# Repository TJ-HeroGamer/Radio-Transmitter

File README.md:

# Radio-Transmitter
Used for theatres to troubleshoot systems. A tool used to remove the issue of a broken radio microphone whilst troubleshooting. This will solely test the radio signal is working properly/ there is no interferance. Everything is very much WIP at the moment. the circuit diagrams will get more complex

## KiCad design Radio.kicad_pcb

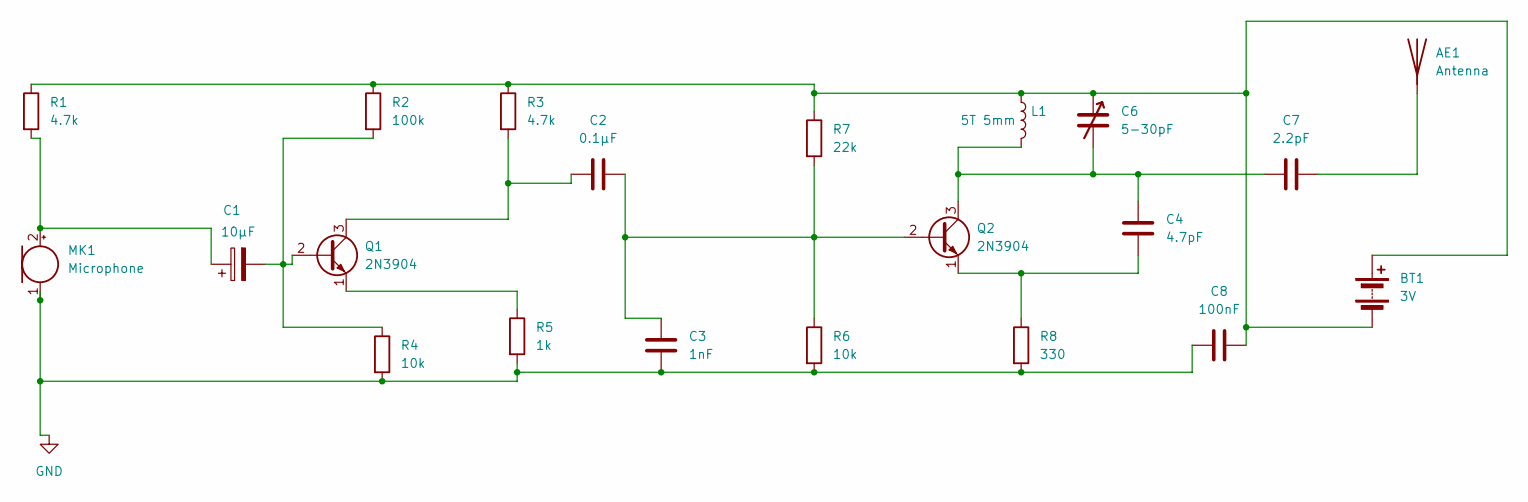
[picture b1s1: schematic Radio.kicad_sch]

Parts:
AE1: Antenna; TestPoint_Pad_D2.0mm
BT1: 3V; PinHeader_1x02_P2.54mm_Vertical
C1: 10μF; CP_Radial_D5.0mm_P2.50mm
C2: 0.1μF; C_Disc_D5.0mm_W2.5mm_P5.00mm
C3: 1nF; C_Disc_D5.0mm_W2.5mm_P5.00mm
C4: 4.7pF; C_Disc_D5.0mm_W2.5mm_P5.00mm
C6: 5-30pF; PinHeader_1x02_P2.54mm_Vertical
C7: 2.2pF; C_Disc_D5.0mm_W2.5mm_P5.00mm
C8: 100nF; C_Disc_D5.0mm_W2.5mm_P5.00mm
L1: 5T 5mm; PinHeader_1x02_P2.54mm_Vertical
MK1: Microphone; PinHeader_1x02_P2.54mm_Vertical
Q1, Q2: 2N3904; TO-92_Inline
R1, R3: 4.7k; R_Axial_DIN0207_L6.3mm_D2.5mm_P10.16mm_Horizontal
R2: 100k; R_Axial_DIN0207_L6.3mm_D2.5mm_P10.16mm_Horizontal
R4, R6: 10k; R_Axial_DIN0207_L6.3mm_D2.5mm_P10.16mm_Horizontal
R5: 1k; R_Axial_DIN0207_L6.3mm_D2.5mm_P10.16mm_Horizontal
R7: 22k; R_Axial_DIN0207_L6.3mm_D2.5mm_P10.16mm_Horizontal
R8: 330; R_Axial_DIN0207_L6.3mm_D2.5mm_P10.16mm_Horizontal

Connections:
GND: C3.1, C8.1, MK1.1 (-), R4.2, R5.2, R6.2, R8.2
unnamed: AE1.1 (A), C7.2
unnamed: BT1.1 (+), BT1.2 (-), C6.1, C8.2, L1.1, R1.1, R2.1, R3.1, R7.1
unnamed: C1.1, MK1.2 (+), R1.2
unnamed: C1.2, Q1.2 (B), R2.2, R4.1
unnamed: C2.1, Q1.3 (C), R3.2
unnamed: Q1.1 (E), R5.1
unnamed: C2.2, C3.2, Q2.2 (B), R6.1, R7.2
unnamed: C4.1, C6.2, C7.1, L1.2, Q2.3 (C)
unnamed: C4.2, Q2.1 (E), R8.1

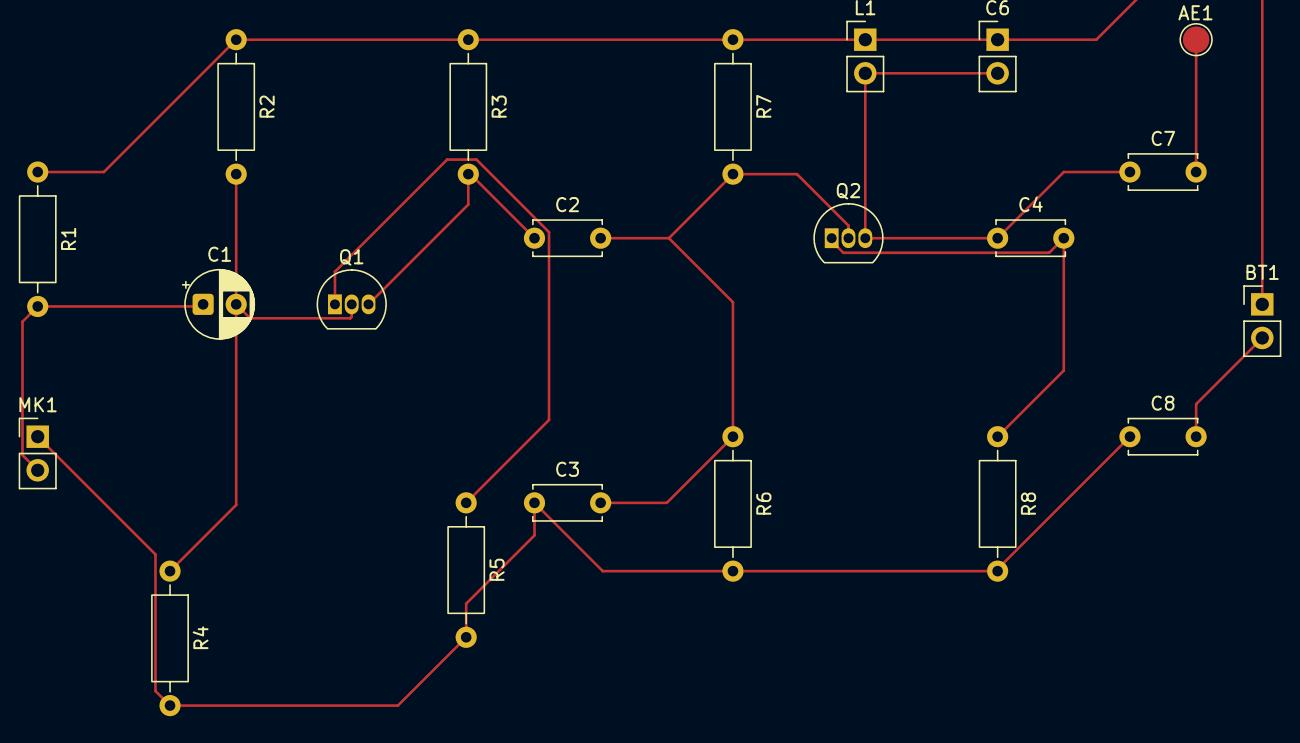
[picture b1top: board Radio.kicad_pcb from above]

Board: 2 copper layers, 21 parts (0 on the bottom side), 10 nets.
